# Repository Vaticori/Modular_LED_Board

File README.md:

# Modular LED Board TMR
Modular PCB to supply power to and control LED strips, providing input for both 5V and 12V. For the Mars Rover of the Toronto Metropolitan Robotics Team

# [View Interactive 3D Model of my PCB!](https://skfb.ly/pACWx)

## Schematic

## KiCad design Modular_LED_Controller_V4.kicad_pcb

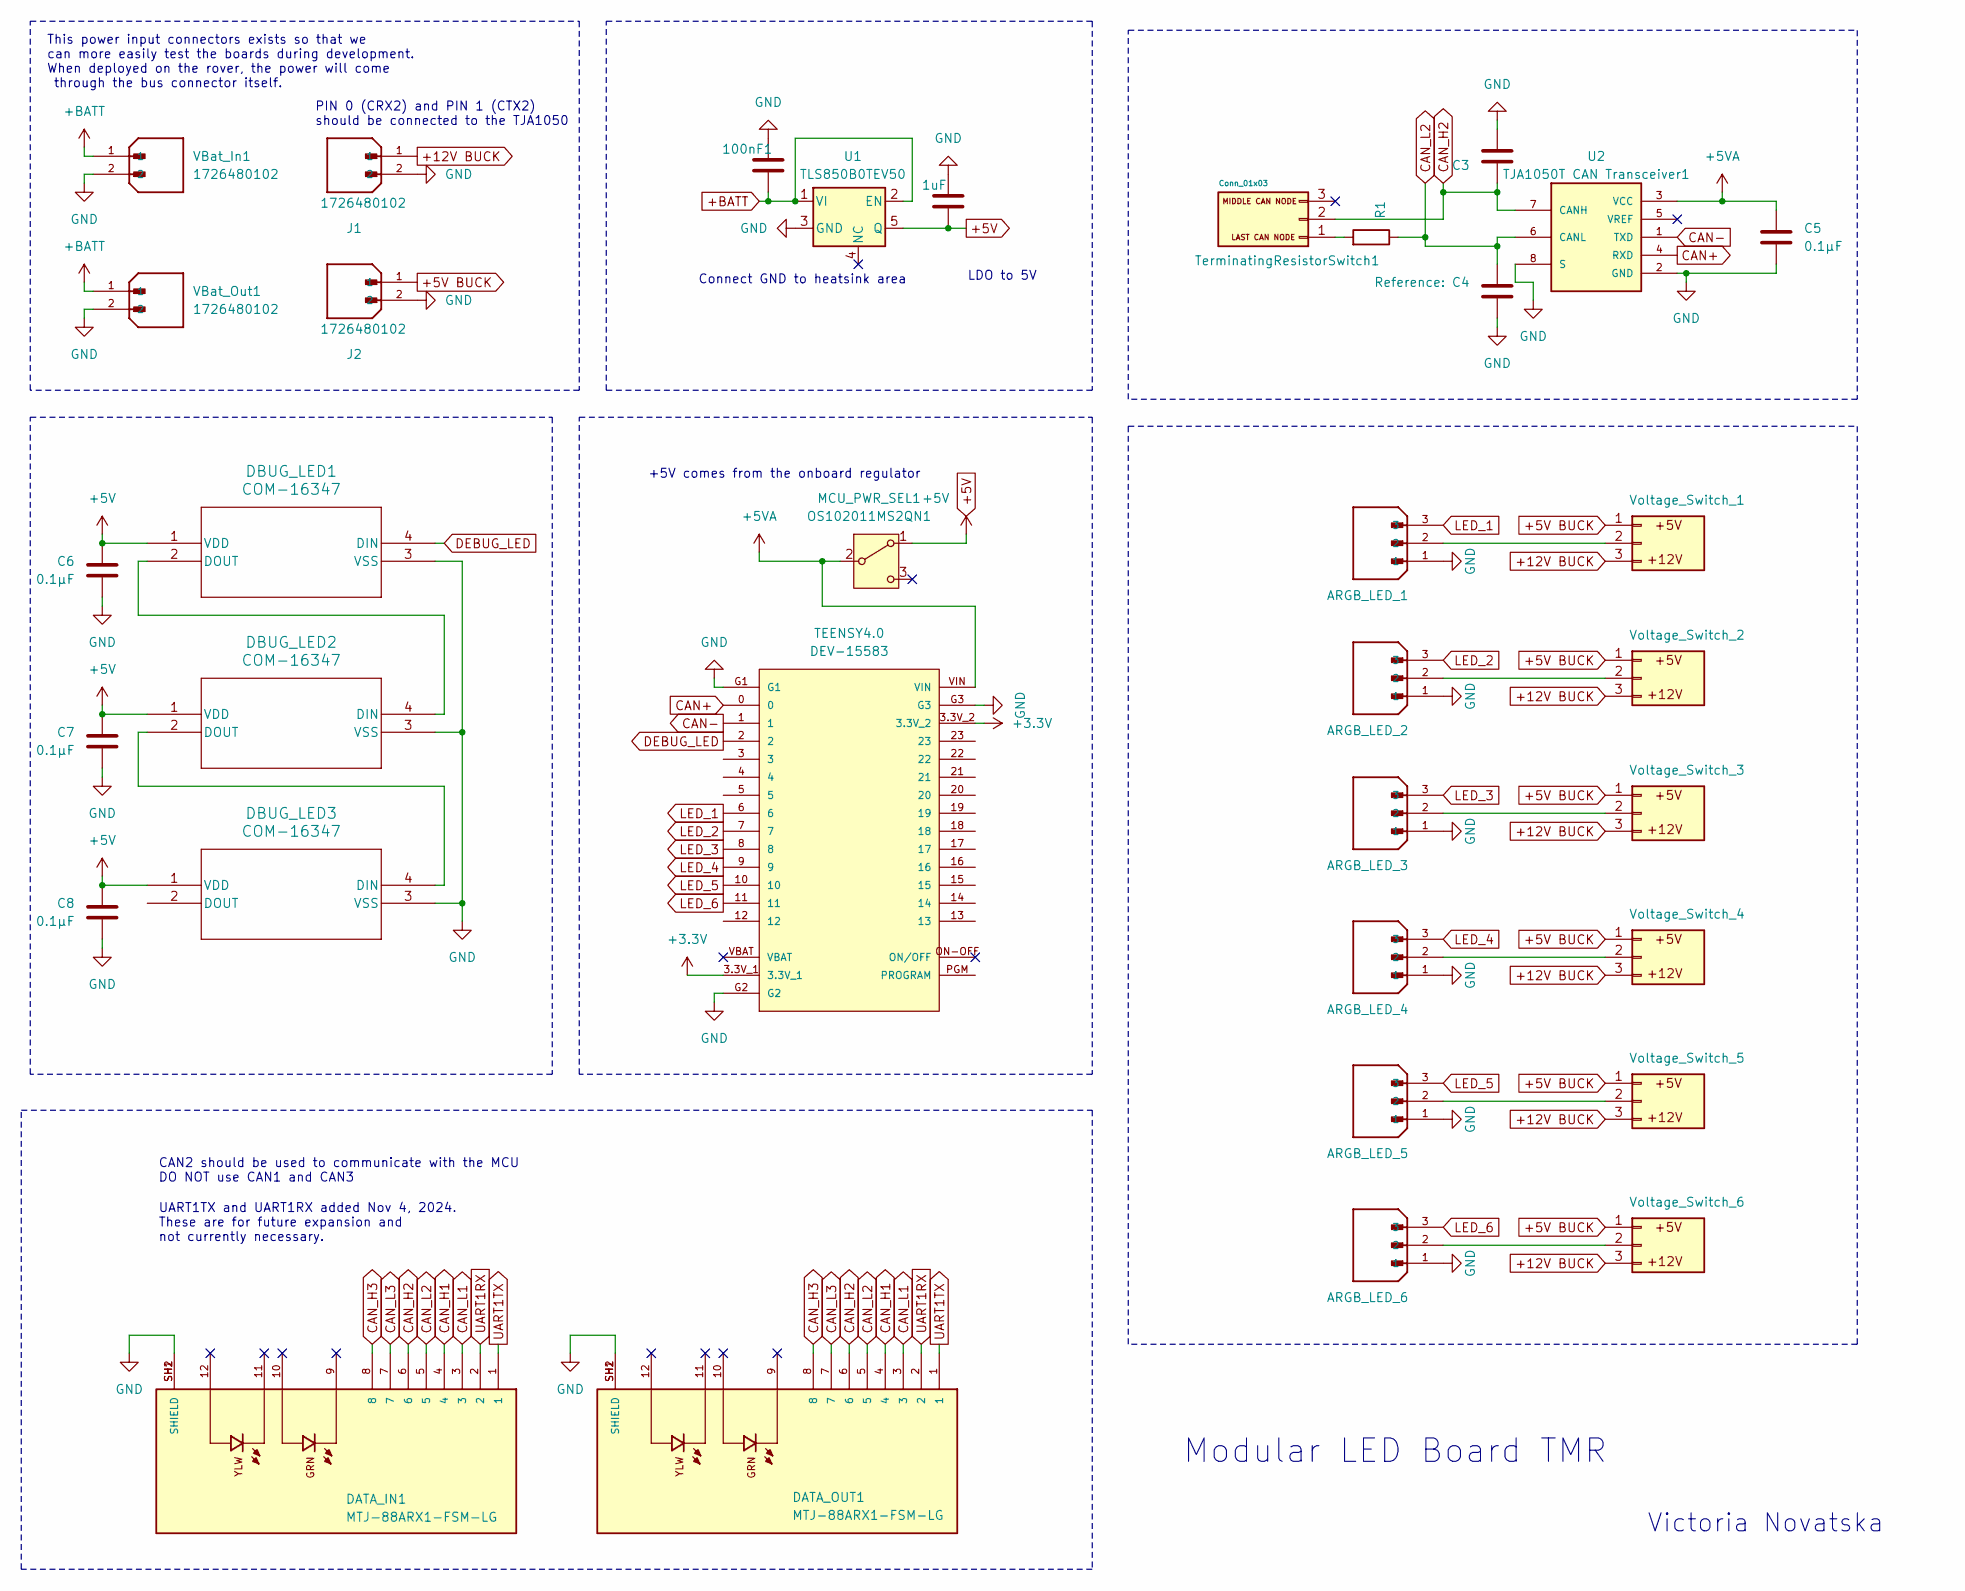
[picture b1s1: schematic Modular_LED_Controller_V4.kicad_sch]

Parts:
ARGB_LED_1, ARGB_LED_2, ARGB_LED_3, ARGB_LED_4, ARGB_LED_5, ARGB_LED_6: B3B-XH-A(LF)(SN); JST_XH_B3B-XH-A_1x03_P2.50mm_Vertical
C1: 100nF1; C_0805_2012Metric_Pad1.18x1.45mm_HandSolder
C2: 1uF; C_0805_2012Metric_Pad1.18x1.45mm_HandSolder
C3: 30pF_1; C_0805_2012Metric_Pad1.18x1.45mm_HandSolder
C4: 30pF; C_0805_2012Metric_Pad1.18x1.45mm_HandSolder
C5, C6, C7, C8: 0.1µF; C_0805_2012Metric_Pad1.18x1.45mm_HandSolder
DATA_IN1: MTJ-88ARX1-FSM-LG; ADAMTECH_MTJ-88ARX1-FSM-LG
DATA_OUT1: MTJ-88ARX1-FSM-LG; ADAMTECH_MTJ-88ARX1-FSM-LG
DBUG_LED1, DBUG_LED2, DBUG_LED3: COM-16347; COM-16347_SPK-M
J1, J2: 1726480102; MOLEX_1726480102; PARTREV A2
MCU_PWR_SEL1: OS102011MS2QN1
R1: 120Ω; R_0805_2012Metric_Pad1.20x1.40mm_HandSolder
TEENSY4.0: DEV-15583; MODULE_DEV-15583
TerminatingResistorSwitch1: Conn_01x03; PinHeader_1x03_P2.54mm_Vertical
U1: TLS850B0TEV50; TO-252-4
U2: TJA1050T CAN Transceiver1; SOT96-1
VBat_In1: 1726480102; MOLEX_1726480102
VBat_Out1: 1726480102; MOLEX_1726480102
Voltage_Switch_1, Voltage_Switch_2, Voltage_Switch_3, Voltage_Switch_4, Voltage_Switch_5, Voltage_Switch_6: PinHeader_1x03_P2.54mm_Vertical

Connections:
+3.3V: TEENSY4.0.3.3V_1, TEENSY4.0.3.3V_2
+5V: C2.1, C6.1, C7.1, C8.1, DBUG_LED1.1 (VDD), DBUG_LED2.1 (VDD), DBUG_LED3.1 (VDD), MCU_PWR_SEL1.1 (A), U1.5 (Q)
+5V BUCK: J2.1, Voltage_Switch_1.1, Voltage_Switch_2.1, Voltage_Switch_3.1, Voltage_Switch_4.1, Voltage_Switch_5.1, Voltage_Switch_6.1
+5VA: C5.1, MCU_PWR_SEL1.2 (B), TEENSY4.0.VIN, U2.3 (VCC)
+12V BUCK: J1.1, Voltage_Switch_1.3, Voltage_Switch_2.3, Voltage_Switch_3.3, Voltage_Switch_4.3, Voltage_Switch_5.3, Voltage_Switch_6.3
+BATT: C1.1, U1.1 (VI), U1.2 (EN), VBat_In1.1, VBat_Out1.1
CAN+: TEENSY4.0.0, U2.4 (RXD)
CAN-: TEENSY4.0.1, U2.1 (TXD)
CAN_H1: DATA_IN1.4, DATA_OUT1.4
CAN_H2: C3.1, DATA_IN1.6, DATA_OUT1.6, TerminatingResistorSwitch1.2, U2.7 (CANH)
CAN_H3: DATA_IN1.8, DATA_OUT1.8
CAN_L1: DATA_IN1.3, DATA_OUT1.3
CAN_L2: C4.1, DATA_IN1.5, DATA_OUT1.5, R1.1, U2.6 (CANL)
CAN_L3: DATA_IN1.7, DATA_OUT1.7
DEBUG_LED: DBUG_LED1.4 (DIN), TEENSY4.0.2
GND: ARGB_LED_1.1, ARGB_LED_2.1, ARGB_LED_3.1, ARGB_LED_4.1, ARGB_LED_5.1, ARGB_LED_6.1, C1.2, C2.2, C3.2, C4.2, C5.2, C6.2, C7.2, C8.2, DATA_IN1.SH1 (SHIELD), DATA_IN1.SH2 (SHIELD), DATA_OUT1.SH1 (SHIELD), DATA_OUT1.SH2 (SHIELD), DBUG_LED1.3 (VSS), DBUG_LED2.3 (VSS), DBUG_LED3.3 (VSS), J1.2, J2.2, TEENSY4.0.G1, TEENSY4.0.G2, TEENSY4.0.G3, U1.3 (GND), U2.2 (GND), U2.8 (S), VBat_In1.2, VBat_Out1.2
LED_1: ARGB_LED_1.3, TEENSY4.0.6
LED_2: ARGB_LED_2.3, TEENSY4.0.7
LED_3: ARGB_LED_3.3, TEENSY4.0.8
LED_4: ARGB_LED_4.3, TEENSY4.0.9
LED_5: ARGB_LED_5.3, TEENSY4.0.10
LED_6: ARGB_LED_6.3, TEENSY4.0.11
unnamed: DBUG_LED1.2 (DOUT), DBUG_LED2.4 (DIN)
unnamed: DBUG_LED2.2 (DOUT), DBUG_LED3.4 (DIN)
unnamed: R1.2, TerminatingResistorSwitch1.1
unnamed: ARGB_LED_1.2, Voltage_Switch_1.2
unnamed: ARGB_LED_2.2, Voltage_Switch_2.2
unnamed: ARGB_LED_3.2, Voltage_Switch_3.2
unnamed: ARGB_LED_4.2, Voltage_Switch_4.2
unnamed: ARGB_LED_5.2, Voltage_Switch_5.2
unnamed: ARGB_LED_6.2, Voltage_Switch_6.2
UART1RX: DATA_IN1.2, DATA_OUT1.2
UART1TX: DATA_IN1.1, DATA_OUT1.1

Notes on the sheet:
+5V comes from the onboard regulator
CAN2 should be used to communicate with the MCU DO NOT use CAN1 and CAN3
This power input connectors exists so that we can more easily test the boards during development. When deployed on the rover, the power will come through the bus connector itself.
Victoria Novatska
PIN 0 (CRX2) and PIN 1 (CTX2) should be connected to the TJA1050
LDO to 5V
Modular LED Board TMR
Connect GND to heatsink area
UART1TX and UART1RX added Nov 4, 2024. These are for future expansion and not currently necessary.

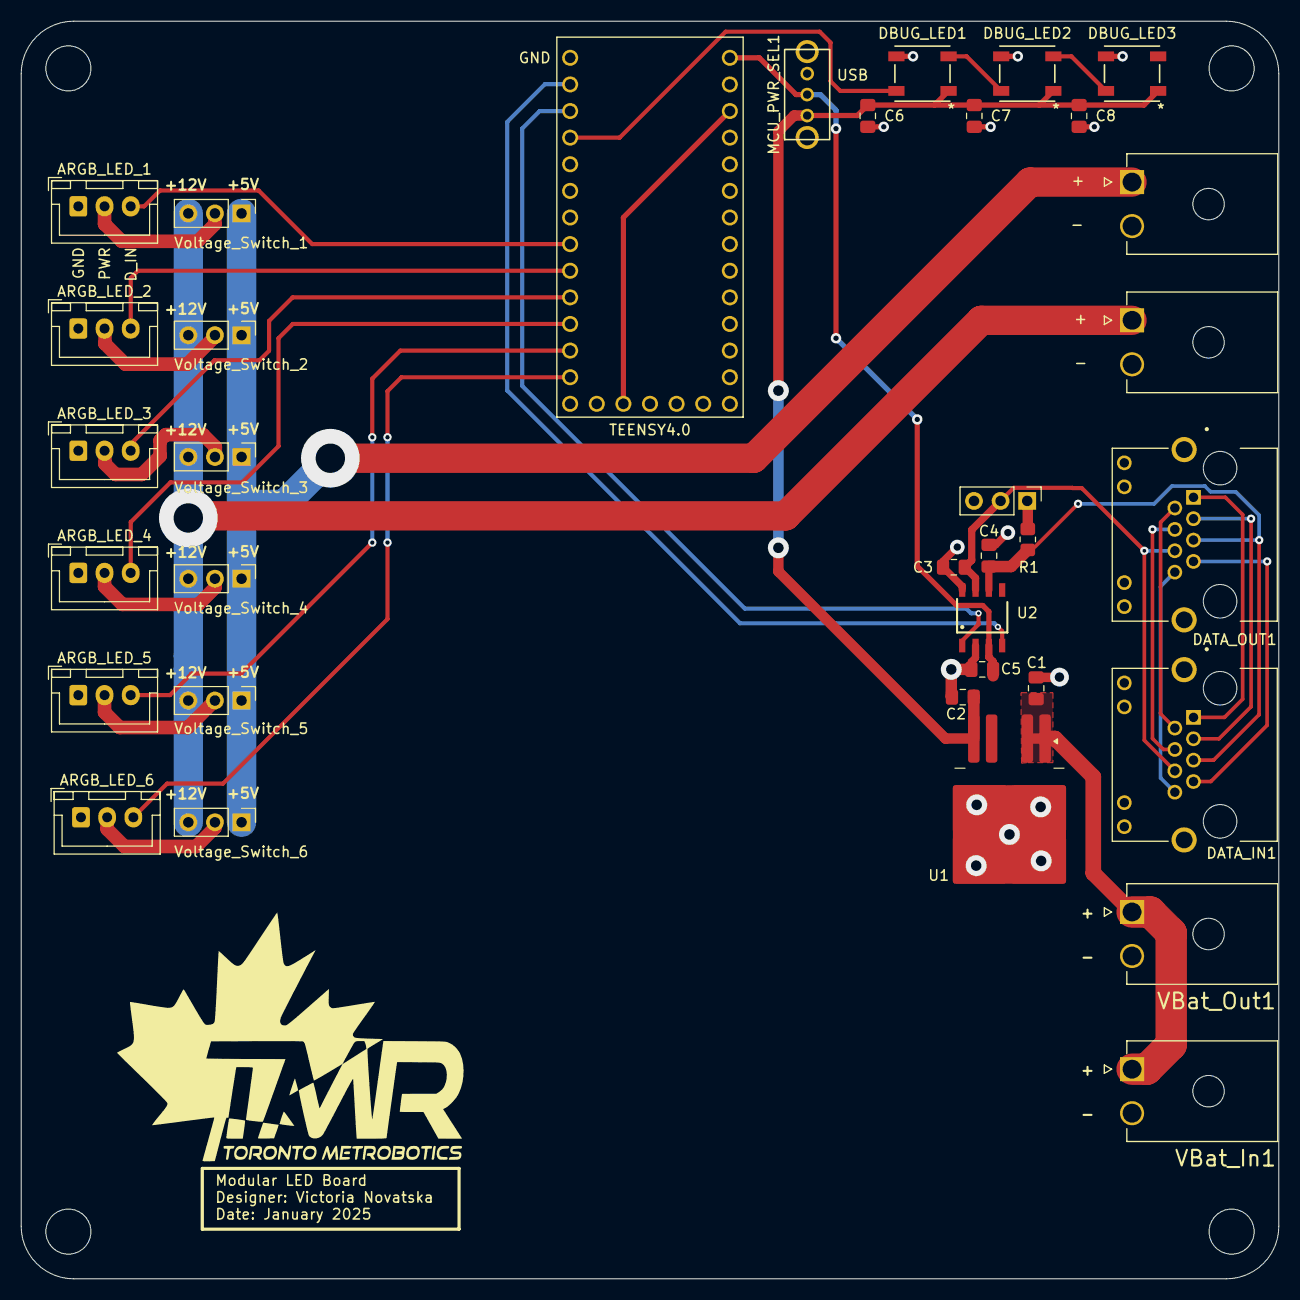
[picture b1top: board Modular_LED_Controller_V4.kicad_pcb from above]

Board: 2 copper layers, 120.0 x 120.0 mm, 35 parts (0 on the bottom side), 33 nets.
